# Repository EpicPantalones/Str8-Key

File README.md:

# The Str8-Key Keyboard

## Introduction

Welcome to Str8-Key, a custom mechanical keyboard in both form and function. Co-designed by Ethan Sorensen and John Rowberry, this ortho-linear, staggered, split keyboard is powered by dual Arduino Pro-Micro microcontrollers and connected via USB-C. Str8-Key bridges a fun engineering project with the great configurability of the QMK firmware, the result of which offers a unique and ergonomically safe typing experience! With 58 keys and infinite possibilities, this keyboard can be used to create layouts tailored perfectly to your workflow (or gameflow!). Built entirely from scratch, it remains an affordable project at just around $140, excluding 3D printing costs — actually a pretty good price for a fully customized typing experience.

Wow this is the 225 recitation! there are so many cool people here today.

## What You'll find in this Github:

You can look in the Tree.txt file to see a full list of all the files contained in the tree. Most of them are specific to our design, but you might find some jumping off points if you're interested in making your own.

## YAML Design

```YAML
metadata:
  engine: 4.0
  version: 1.2
  author: John Rowberry
  contact: johnrowberries@gmail.com
units:
  default_spread: 'cx'
  default_splay: 0
  default_width: 'cy'
  default_padding: 'cx'
  default_autobind: 10
  xspace: cx
  yspace: cy
  paddingy: yspace
...
and more
```

YAML (YAML Ain't Markup Language) is a human-readable data serialization format often used for configuration files. It focuses on simplicity and uses indentation to represent structure, making it easy to read and write. YAML supports key-value pairs, lists, and nested structures, and it's useful to us because Ergogen uses YAML structures to generate layouts for custom keyboards. Look at Flatfox's guide (linked below) for more info on the structure of the YAML code, but its really simple and in most cases you can reference an example like our code and get the right result.

## Board Layout

## Final Product

## Resources we can provide for your own design:

The [**Ergogen guide by FlatFootFox**](https://flatfootfox.com/ergogen-introduction/) was instrumental in helping us bring Str8-Key to life, serving as both a comprehensive resource and our virtual teacher, alongside guidance from **BYU's IEEE Club**. Initially, we used the [**Ergogen Unofficial Website**](https://ergogen.cache.works/), which offers better real-time rendering in some cases compared to the [official site](https://ergogen.xyz/), but we eventually transitioned to running **Ergogen locally on Node**, as suggested in FlatFootFox's guide, for even greater control. [**QMK Firmware**](https://qmk.fm/) was chosen to program the keyboard, and though this is still a work in progress, it offers immense flexibility. Additionally, [**Carter's GitHub**](https://github.com/Virginia2244/BYU-IEEE-Keyboard-Project) project was invaluable, providing a template for the YAML files and saving us on more than one occasion during the build process.

## Resources for the footprint creation and KiCad stuff:

The documentation for the LEDs we chose came from the same **[Adafruit link where we purchased them](https://www.adafruit.com/product/4684)**, and I used this **[SNAP EDA footprint](https://www.snapeda.com/parts/WS2812-2020/Worldsemi/view-part/?company=BYU&)** as a starting point for the Ergogen code found in `footprints/epicpantalones/WS2812`. To ensure the choc switches fit and aligned properly, I referenced this **[choc switch datasheet](https://cdn-shop.adafruit.com/product-files/5113/CHOC+keyswitch_Kailh-CPG135001D01_C400229.pdf)**. The Ergogen code I wrote was primarily based on a guide to **[converting KiCad footprints to Ergogen](https://nilnil.notion.site/Convert-Kicad-Footprints-to-Ergogen-8340ce87ad554c69af4e3f92bc9a0898#03eb03c468ba49feabb4847096c0ff94)**, with some additional reference from this **[LED code](https://github.com/infused-kim/kb_ergogen_fp/blob/main/smd_0805.js)** that I used as a basis.

## The actual parts that we purchased:

We ordered the PCB from **[JLCPCB](https://jlcpcb.com/)**, and the price was incredibly affordable at just $13 plus shipping, totaling about $30 for five boards. The keys cost around $50, depending on the type, and we opted for **[frosted black choc switch keycaps](https://a.co/d/dT4MgD5)**, as the frosted look let the RGB lighting through. The LEDs were sourced from **[Adafruit](https://www.adafruit.com/product/4684)**. Our controller head unit is the **[Arduino Pro Micro](https://www.sparkfun.com/products/12640)**, a board we discovered during this project, and they are connected via an audio connector (links forthcoming). We also included hot-swap sockets for the choc switches, which makes customization easy, and control flow diodes, although we don't have the sourcing details or costs for those at the moment.

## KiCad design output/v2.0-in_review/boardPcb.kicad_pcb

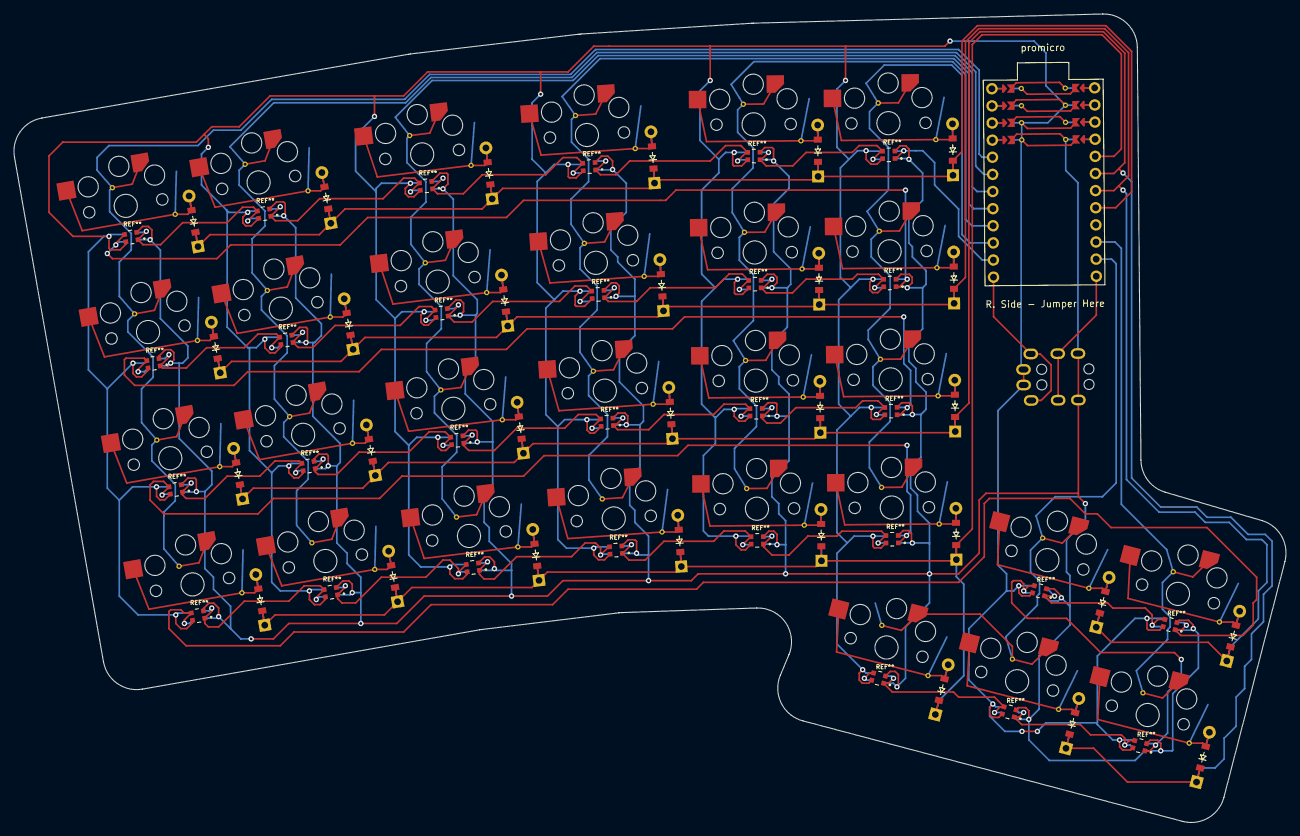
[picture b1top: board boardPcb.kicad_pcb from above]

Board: 2 copper layers, 188.6 x 119.9 mm, 59 parts (0 on the bottom side), 41 nets.

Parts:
D1, D2, D3, D4, D5, D6, D7, D8, D9, D10, D11, D12, D13, D14, D15, D16, D17, D18, D19, D20, D21, D22, D23, D24, D25, D26, D27, D28, D29: ComboDiode
S1, S2, S3, S4, S5, S6, S7, S8, S9, S10, S11, S12, S13, S14, S15, S16, S17, S18, S19, S20, S21, S22, S23, S24, S25, S26, S27, S28, S29: PG1350
TRRS1: TRRS-PJ-320A-dual

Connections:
P2: S1.1, S1.2, S2.1, S2.2, S3.1, S3.2, S4.1, S4.2
P3: S5.1, S5.2, S6.1, S6.2, S7.1, S7.2, S8.1, S8.2
P4: S9.1, S9.2, S10.1, S10.2, S11.1, S11.2, S12.1, S12.2
P5: S13.1, S13.2, S14.1, S14.2, S15.1, S15.2, S16.1, S16.2
P6: S17.1, S17.2, S18.1, S18.2, S19.1, S19.2, S20.1, S20.2
P7: S21.1, S21.2, S22.1, S22.2, S23.1, S23.2, S24.1, S24.2
P14: S27.1, S27.2, S29.1, S29.2
P16: S25.1, S25.2, S26.1, S26.2, S28.1, S28.2
P18: D4.1, D8.1, D12.1, D16.1, D20.1, D24.1
P19: D3.1, D7.1, D11.1, D15.1, D19.1, D23.1, D28.1, D29.1
P20: D2.1, D6.1, D10.1, D14.1, D18.1, D22.1, D26.1, D27.1
P21: D1.1, D5.1, D9.1, D13.1, D17.1, D21.1, D25.1
far2_thumb2: D29.2, S29.2
far_thumb: D27.2, S27.2
home2_thumb2: D28.2, S28.2
home_thumb: D26.2, S26.2
middle_bottom: D13.2, S13.2
middle_middle: D14.2, S14.2
middle_number: D16.2, S16.2
middle_top: D15.2, S15.2
near_thumb: D25.2, S25.2
pink2_bottom: D5.2, S5.2
pink2_middle: D6.2, S6.2
pink2_number: D8.2, S8.2
pink2_top: D7.2, S7.2
pinky1_bottom: D1.2, S1.2
pinky1_middle: D2.2, S2.2
pinky1_number: D4.2, S4.2
pinky1_top: D3.2, S3.2
pointer2_bottom: D21.2, S21.2
pointer2_middle: D22.2, S22.2
pointer2_number: D24.2, S24.2
pointer2_top: D23.2, S23.2
pointer_bottom: D17.2, S17.2
pointer_middle: D18.2, S18.2
pointer_number: D20.2, S20.2
pointer_top: D19.2, S19.2
ring_bottom: D9.2, S9.2
ring_middle: D10.2, S10.2
ring_number: D12.2, S12.2
ring_top: D11.2, S11.2

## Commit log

2023-11-09 Create Keyboard YAML
    First
2023-11-09 Update Keyboard YAML
2023-11-30 Update Keyboard YAML
    Finished background
2024-02-02 Updates I did with Carter on Wed
2024-02-02 Aesthetics Update 1.0
2024-02-08 Updated PCB outline
    Now contains enough room to fit keyboard controller (0.7in x 1.3in or ~18mm x 33mm) with ~5mm excess
2024-02-08 Updated outline again
2024-02-08 final outline update - send to print
2024-02-08 PCB updates :D
2024-02-16 Moved audio jack
2024-02-16 moved keyboard to the center of the page
2024-02-16 file rename
2024-02-16 Running local Ergogen now
2024-02-16 created some PCB stuff; prep for layout
2024-02-27 ready to do official layout
2024-02-27 finished initial layout; pending 3 reviews
2024-02-27 tweak two remove 2 redundant vias
2024-03-01 Layout reviewed; revision 2
2024-03-02 downloaded some help docs
2024-03-02 cleaned stuff
2024-03-02 created custom LED footprint
2024-03-02 renamed folder for clarity
2024-03-02 fixed readme added new links
2024-03-02 testing new footprint - almost redy to relayout
2024-03-02 added parts links
2024-03-04 finished rev. 2.0 with 2x2 LEDs; review time
2024-03-04 Added plugin I used for net names as ref
2024-03-04 created final output version; sent for creation!
2024-03-04 Turned README into a proper frontpage
2024-03-04 typo on frontpage description
2024-03-04 added photos (I'm not proud or anything)
2024-03-29 Create WithCaseInfo
    Same project but minus the pcb and plus the case info
2024-06-25 Added some test cases files - we shall see
2024-06-26 Modified case for magnets and made it slightly big
2024-06-26 Unfinished Lid added
2024-06-27 added final (hopefully) model of case
2024-06-28 first attempt at lid
2024-07-01 copied Carter's template; making my own
2024-07-12 added working firmware
2024-09-20 making new case
2024-09-20 added better photos
2024-09-20 Made some more serious documentation
2024-09-20 the 225 commit
